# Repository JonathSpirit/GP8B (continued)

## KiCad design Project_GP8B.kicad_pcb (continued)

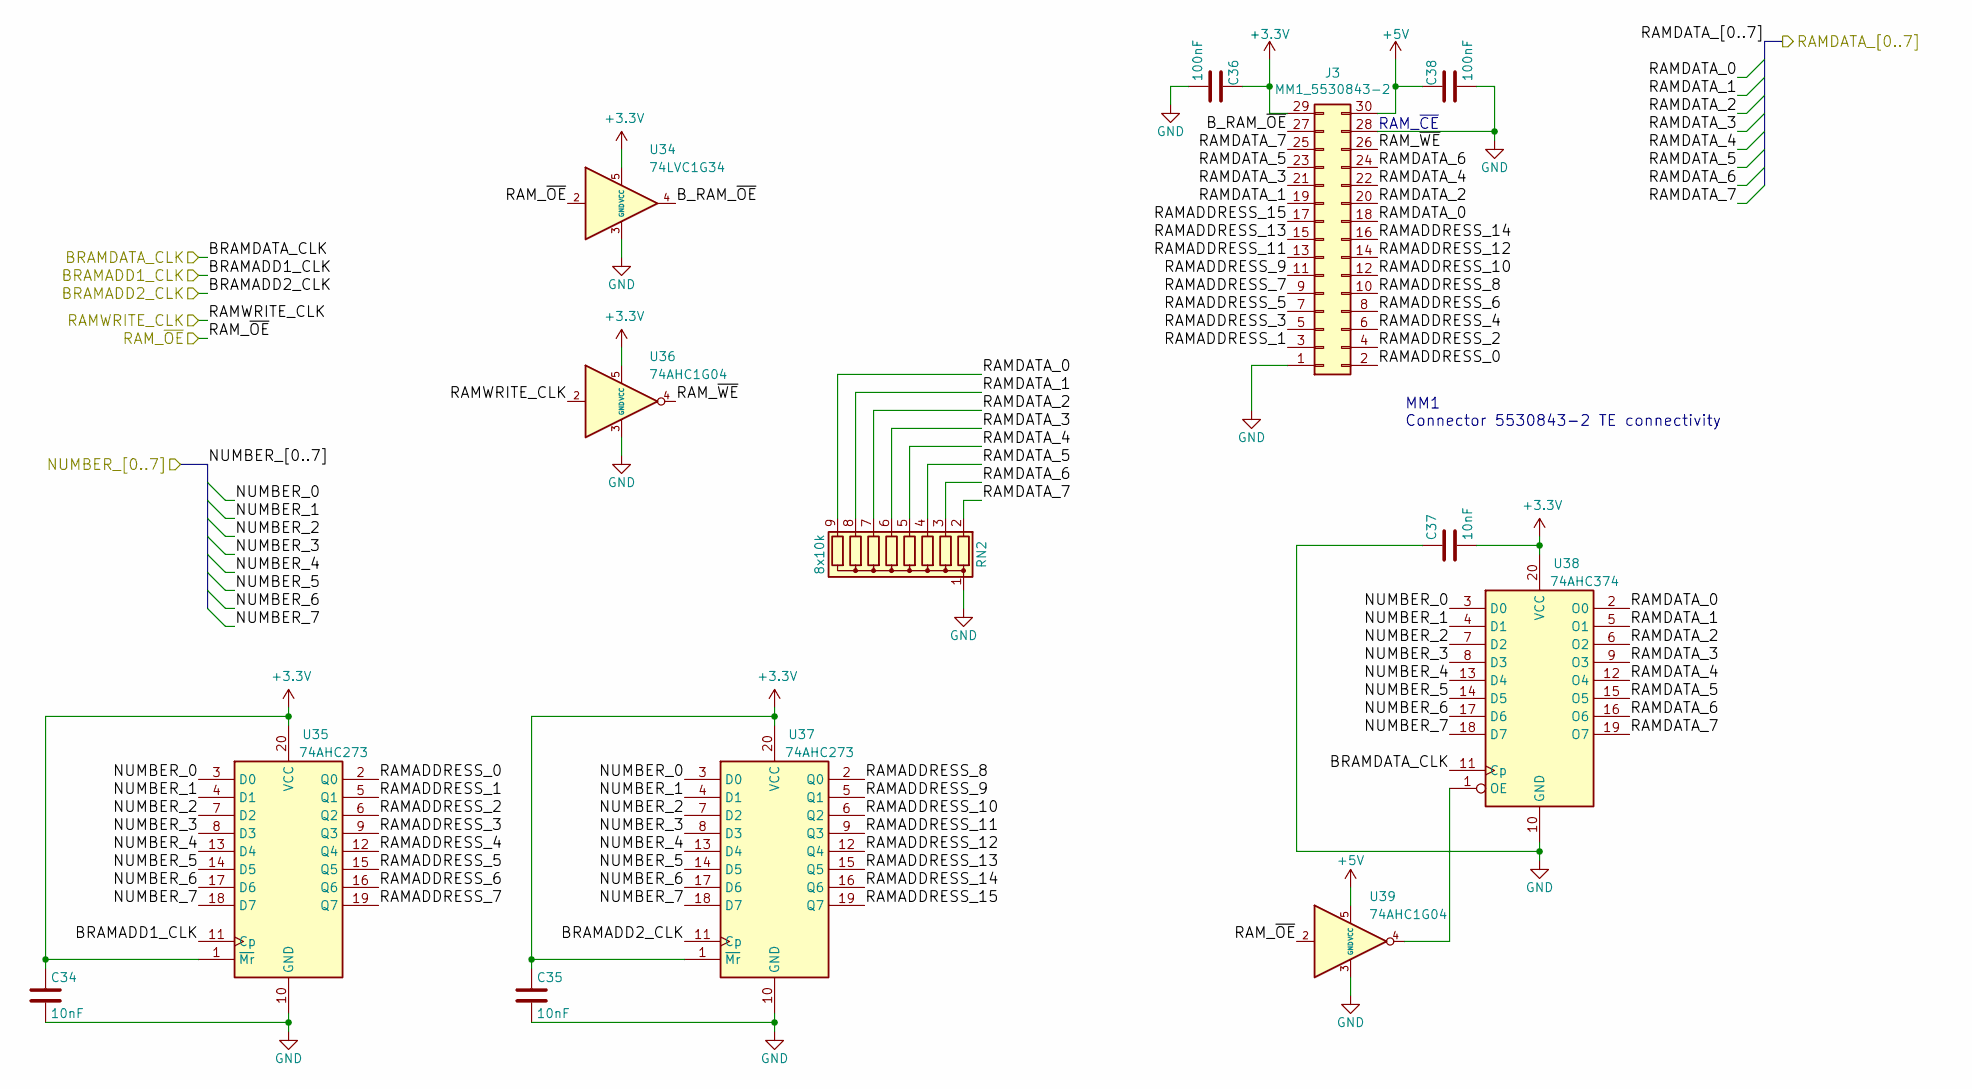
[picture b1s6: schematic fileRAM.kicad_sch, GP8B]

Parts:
C34, C35, C37: 10nF; C_0805_2012Metric
C36, C38: 100nF; C_0805_2012Metric
J3: MM1_5530843-2; TE_5530843-2
RN2: 8x10k; R_Array_SIP9
U34: 74LVC1G34; SOT-23-5
U35, U37: 74AHC273; SOIC-20W_7.5x12.8mm_P1.27mm
U36, U39: 74AHC1G04; SOT-23-5
U38: 74AHC374; SOIC-20W_7.5x12.8mm_P1.27mm

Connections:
+3V3: C34.1, C35.1, C36.1, C37.2, J3.29, U34.5 (VCC), U35.1 (~Mr), U35.20 (VCC), U36.5 (VCC), U37.1 (~Mr), U37.20 (VCC), U38.20 (VCC); also elsewhere on the board
+5V: C38.1, J3.30, U39.5 (VCC); also elsewhere on the board
/BRAMADD1_CLK: U35.11 (Cp); also elsewhere on the board
/BRAMADD2_CLK: U37.11 (Cp); also elsewhere on the board
/BRAMDATA_CLK: U38.11 (Cp); also elsewhere on the board
/NUMBER_0: U35.3 (D0), U37.3 (D0), U38.3 (D0); also elsewhere on the board
/NUMBER_1: U35.4 (D1), U37.4 (D1), U38.4 (D1); also elsewhere on the board
/NUMBER_2: U35.7 (D2), U37.7 (D2), U38.7 (D2); also elsewhere on the board
/NUMBER_3: U35.8 (D3), U37.8 (D3), U38.8 (D3); also elsewhere on the board
/NUMBER_4: U35.13 (D4), U37.13 (D4), U38.13 (D4); also elsewhere on the board
/NUMBER_5: U35.14 (D5), U37.14 (D5), U38.14 (D5); also elsewhere on the board
/NUMBER_6: U35.17 (D6), U37.17 (D6), U38.17 (D6); also elsewhere on the board
/NUMBER_7: U35.18 (D7), U37.18 (D7), U38.18 (D7); also elsewhere on the board
/NumberSelect/RAMDATA_0: J3.18, RN2.9 (R8), U38.2 (O0); also elsewhere on the board
/NumberSelect/RAMDATA_1: J3.19, RN2.8 (R7), U38.5 (O1); also elsewhere on the board
/NumberSelect/RAMDATA_2: J3.20, RN2.7 (R6), U38.6 (O2); also elsewhere on the board
/NumberSelect/RAMDATA_3: J3.21, RN2.6 (R5), U38.9 (O3); also elsewhere on the board
/NumberSelect/RAMDATA_4: J3.22, RN2.5 (R4), U38.12 (O4); also elsewhere on the board
/NumberSelect/RAMDATA_5: J3.23, RN2.4 (R3), U38.15 (O5); also elsewhere on the board
/NumberSelect/RAMDATA_6: J3.24, RN2.3 (R2), U38.16 (O6); also elsewhere on the board
/NumberSelect/RAMDATA_7: J3.25, RN2.2 (R1), U38.19 (O7); also elsewhere on the board
/RAM/B_RAM_~OE: J3.27, U34.4
/RAM/RAMADDRESS_0: J3.2, U35.2 (Q0)
/RAM/RAMADDRESS_1: J3.3, U35.5 (Q1)
/RAM/RAMADDRESS_2: J3.4, U35.6 (Q2)
/RAM/RAMADDRESS_3: J3.5, U35.9 (Q3)
/RAM/RAMADDRESS_4: J3.6, U35.12 (Q4)
/RAM/RAMADDRESS_5: J3.7, U35.15 (Q5)
/RAM/RAMADDRESS_6: J3.8, U35.16 (Q6)
/RAM/RAMADDRESS_7: J3.9, U35.19 (Q7)
/RAM/RAMADDRESS_8: J3.10, U37.2 (Q0)
/RAM/RAMADDRESS_9: J3.11, U37.5 (Q1)
/RAM/RAMADDRESS_10: J3.12, U37.6 (Q2)
/RAM/RAMADDRESS_11: J3.13, U37.9 (Q3)
/RAM/RAMADDRESS_12: J3.14, U37.12 (Q4)
/RAM/RAMADDRESS_13: J3.15, U37.15 (Q5)
/RAM/RAMADDRESS_14: J3.16, U37.16 (Q6)
/RAM/RAMADDRESS_15: J3.17, U37.19 (Q7)
/RAM/RAM_~WE: J3.26, U36.4
/RAMWRITE_CLK: U36.2; also elsewhere on the board
/RAM_OE_CONTROL: U34.2, U39.2; also elsewhere on the board
unnamed: U38.1 (OE), U39.4

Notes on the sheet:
MM1 Connector 5530843-2 TE connectivity
RAM_~{CE}

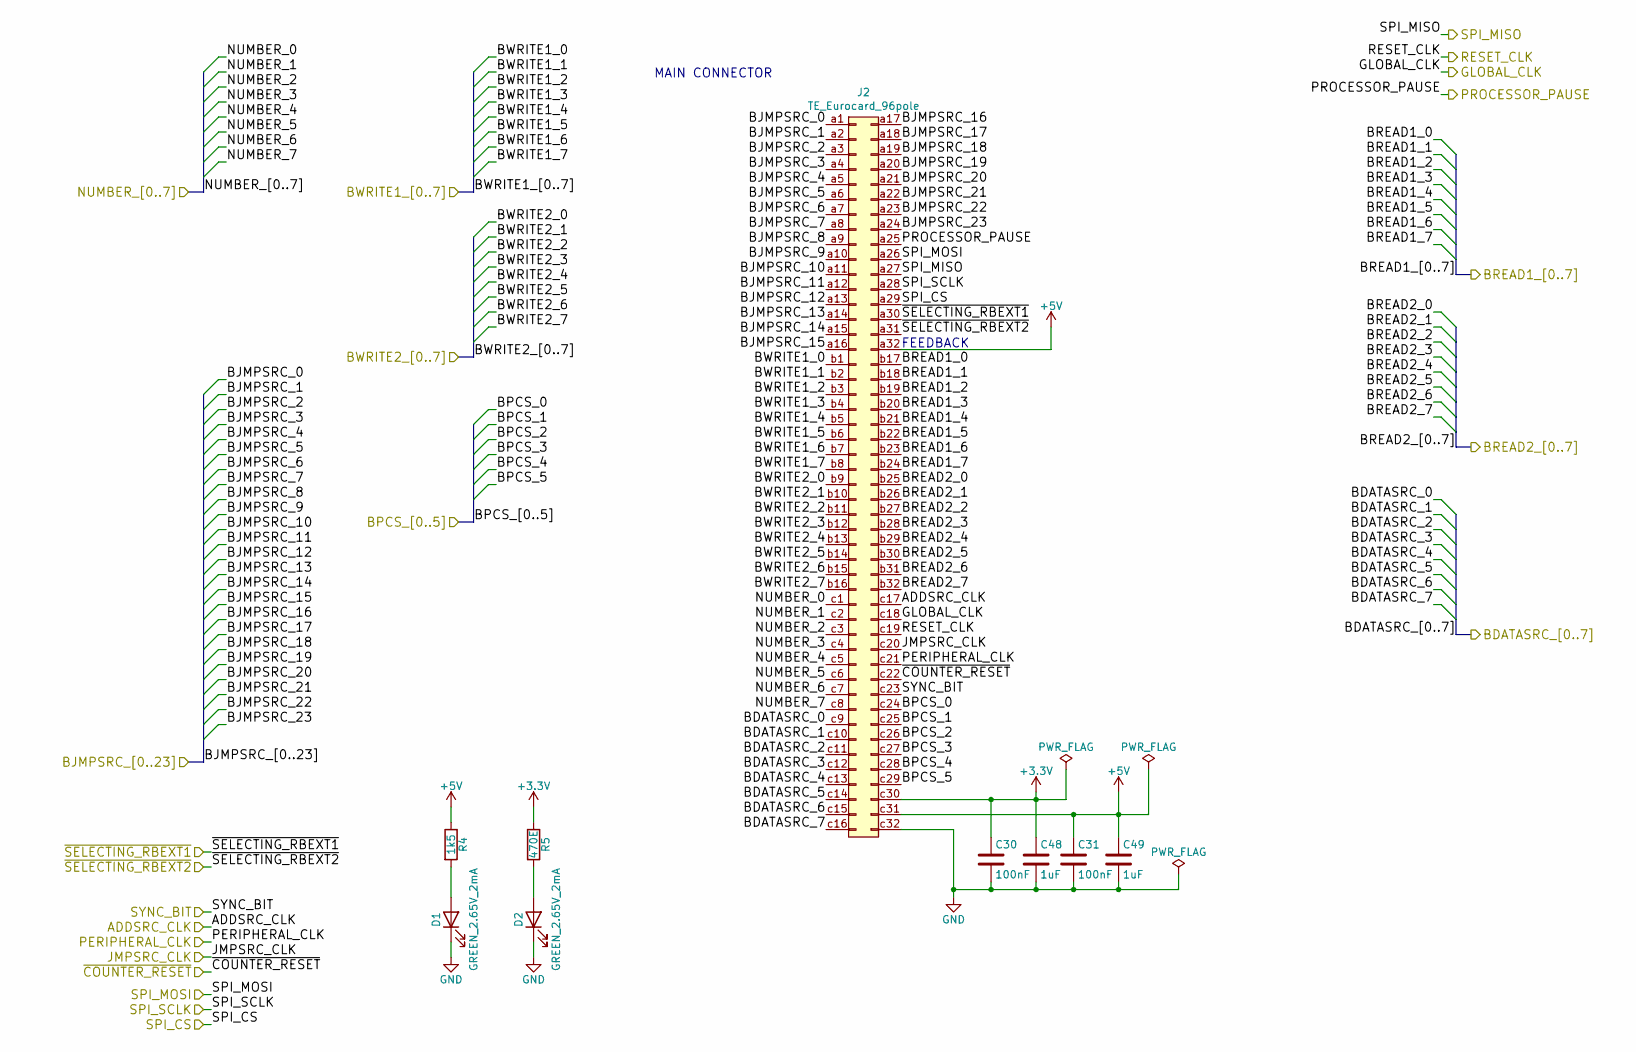
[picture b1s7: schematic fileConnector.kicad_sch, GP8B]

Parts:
C30, C31: 100nF; C_0805_2012Metric
C48, C49: 1uF; C_0805_2012Metric
D1, D2: GREEN_2.65V_2mA; LED_1206_3216Metric
J2: TE_Eurocard_96pole; Eurocard_5536475-1
R4: 1k5; R_0805_2012Metric
R5: 470E; R_0805_2012Metric

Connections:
+3V3: C30.1, C48.1, J2.c30, R5.1; also elsewhere on the board
+5V: C31.1, C49.1, J2.a32, J2.c31, R4.1; also elsewhere on the board
/ADDSRC_CLK: J2.c17; also elsewhere on the board
/Connector/BDATASRC_0: J2.c9; also elsewhere on the board
/Connector/BDATASRC_1: J2.c10; also elsewhere on the board
/Connector/BDATASRC_2: J2.c11; also elsewhere on the board
/Connector/BDATASRC_3: J2.c12; also elsewhere on the board
/Connector/BDATASRC_4: J2.c13; also elsewhere on the board
/Connector/BDATASRC_5: J2.c14; also elsewhere on the board
/Connector/BDATASRC_6: J2.c15; also elsewhere on the board
/Connector/BDATASRC_7: J2.c16; also elsewhere on the board
/Connector/BJMPSRC_0: J2.a1; also elsewhere on the board
/Connector/BJMPSRC_1: J2.a2; also elsewhere on the board
/Connector/BJMPSRC_2: J2.a3; also elsewhere on the board
/Connector/BJMPSRC_3: J2.a4; also elsewhere on the board
/Connector/BJMPSRC_4: J2.a5; also elsewhere on the board
/Connector/BJMPSRC_5: J2.a6; also elsewhere on the board
/Connector/BJMPSRC_6: J2.a7; also elsewhere on the board
/Connector/BJMPSRC_7: J2.a8; also elsewhere on the board
/Connector/BJMPSRC_8: J2.a9; also elsewhere on the board
/Connector/BJMPSRC_9: J2.a10; also elsewhere on the board
/Connector/BJMPSRC_10: J2.a11; also elsewhere on the board
/Connector/BJMPSRC_11: J2.a12; also elsewhere on the board
/Connector/BJMPSRC_12: J2.a13; also elsewhere on the board
/Connector/BJMPSRC_13: J2.a14; also elsewhere on the board
/Connector/BJMPSRC_14: J2.a15; also elsewhere on the board
/Connector/BJMPSRC_15: J2.a16; also elsewhere on the board
/Connector/BJMPSRC_16: J2.a17; also elsewhere on the board
/Connector/BJMPSRC_17: J2.a18; also elsewhere on the board
/Connector/BJMPSRC_18: J2.a19; also elsewhere on the board
/Connector/BJMPSRC_19: J2.a20; also elsewhere on the board
/Connector/BJMPSRC_20: J2.a21; also elsewhere on the board
/Connector/BJMPSRC_21: J2.a22; also elsewhere on the board
/Connector/BJMPSRC_22: J2.a23; also elsewhere on the board
/Connector/BJMPSRC_23: J2.a24; also elsewhere on the board
/Connector/BPCS_0: J2.c24; also elsewhere on the board
/Connector/BPCS_1: J2.c25; also elsewhere on the board
/Connector/BPCS_2: J2.c26; also elsewhere on the board
/Connector/BPCS_3: J2.c27; also elsewhere on the board
/Connector/BPCS_4: J2.c28; also elsewhere on the board
/Connector/BPCS_5: J2.c29; also elsewhere on the board
/Connector/BREAD1_0: J2.b17; also elsewhere on the board
/Connector/BREAD1_1: J2.b18; also elsewhere on the board
/Connector/BREAD1_2: J2.b19; also elsewhere on the board
/Connector/BREAD1_3: J2.b20; also elsewhere on the board
/Connector/BREAD1_4: J2.b21; also elsewhere on the board
/Connector/BREAD1_5: J2.b22; also elsewhere on the board
/Connector/BREAD1_6: J2.b23; also elsewhere on the board
/Connector/BREAD1_7: J2.b24; also elsewhere on the board
/Connector/BREAD2_0: J2.b25; also elsewhere on the board
/Connector/BREAD2_1: J2.b26; also elsewhere on the board
/Connector/BREAD2_2: J2.b27; also elsewhere on the board
/Connector/BREAD2_3: J2.b28; also elsewhere on the board
/Connector/BREAD2_4: J2.b29; also elsewhere on the board
/Connector/BREAD2_5: J2.b30; also elsewhere on the board
/Connector/BREAD2_6: J2.b31; also elsewhere on the board
/Connector/BREAD2_7: J2.b32; also elsewhere on the board
/Connector/BWRITE1_0: J2.b1; also elsewhere on the board
/Connector/BWRITE1_1: J2.b2; also elsewhere on the board
/Connector/BWRITE1_2: J2.b3; also elsewhere on the board
/Connector/BWRITE1_3: J2.b4; also elsewhere on the board
/Connector/BWRITE1_4: J2.b5; also elsewhere on the board
/Connector/BWRITE1_5: J2.b6; also elsewhere on the board
/Connector/BWRITE1_6: J2.b7; also elsewhere on the board
/Connector/BWRITE1_7: J2.b8; also elsewhere on the board
/Connector/BWRITE2_0: J2.b9; also elsewhere on the board
/Connector/BWRITE2_1: J2.b10; also elsewhere on the board
/Connector/BWRITE2_2: J2.b11; also elsewhere on the board
/Connector/BWRITE2_3: J2.b12; also elsewhere on the board
/Connector/BWRITE2_4: J2.b13; also elsewhere on the board
/Connector/BWRITE2_5: J2.b14; also elsewhere on the board
/Connector/BWRITE2_6: J2.b15; also elsewhere on the board
/Connector/BWRITE2_7: J2.b16; also elsewhere on the board
/GLOBAL_CLK: J2.c18; also elsewhere on the board
/JMPSRC_CLK: J2.c20; also elsewhere on the board
/NUMBER_0: J2.c1; also elsewhere on the board
/NUMBER_1: J2.c2; also elsewhere on the board
/NUMBER_2: J2.c3; also elsewhere on the board
/NUMBER_3: J2.c4; also elsewhere on the board
/NUMBER_4: J2.c5; also elsewhere on the board
/NUMBER_5: J2.c6; also elsewhere on the board
/NUMBER_6: J2.c7; also elsewhere on the board
/NUMBER_7: J2.c8; also elsewhere on the board
/PERIPHERAL_CLK: J2.c21; also elsewhere on the board
/PROCESSOR_PAUSE: J2.a25; also elsewhere on the board
/RESET_CLK: J2.c19; also elsewhere on the board
/SPI_CS: J2.a29; also elsewhere on the board
/SPI_MISO: J2.a27; also elsewhere on the board
/SPI_MOSI: J2.a26; also elsewhere on the board
/SPI_SCLK: J2.a28; also elsewhere on the board
/SYNC_BIT: J2.c23; also elsewhere on the board
/~COUNTER_RESET: J2.c22; also elsewhere on the board
/~SELECTING_RBEXT1: J2.a30; also elsewhere on the board
/~SELECTING_RBEXT2: J2.a31; also elsewhere on the board
unnamed: D1.2 (A), R4.2
unnamed: D2.2 (A), R5.2

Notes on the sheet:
MAIN CONNECTOR
FEEDBACK

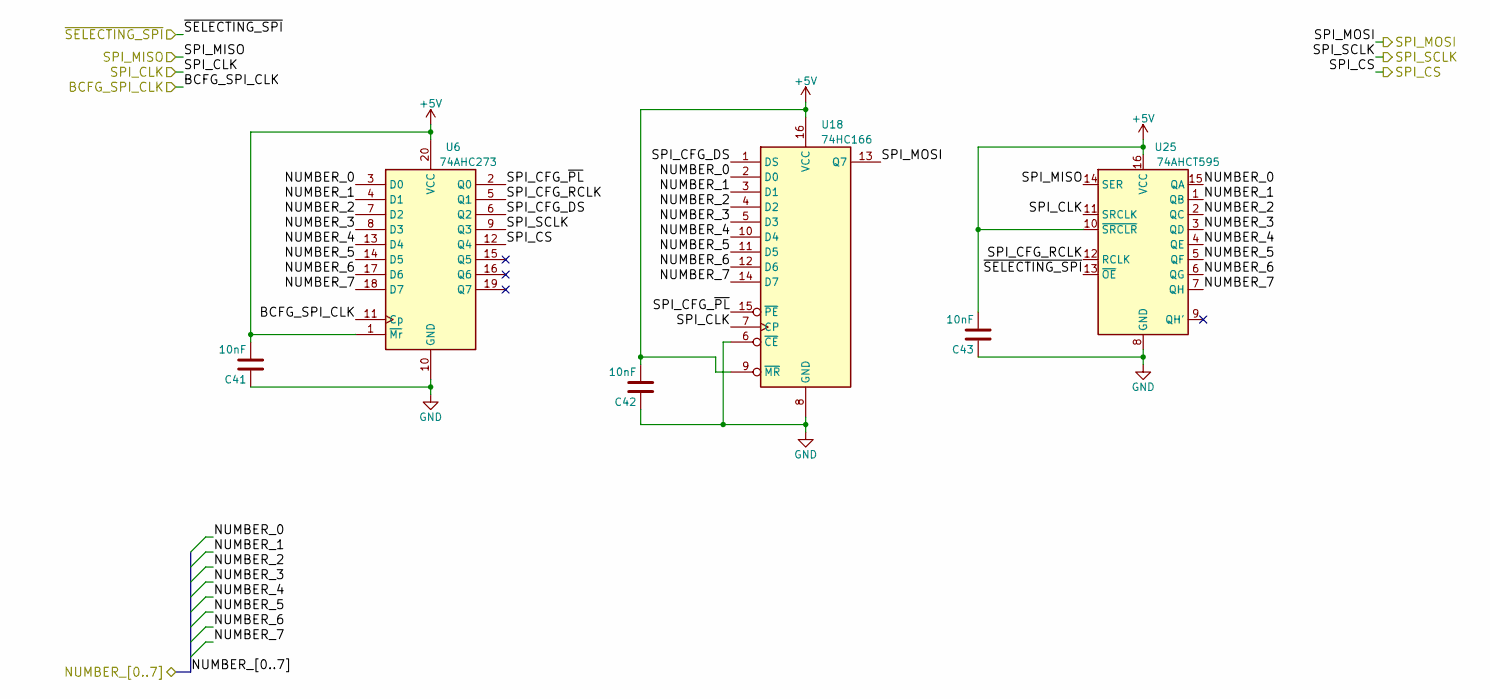
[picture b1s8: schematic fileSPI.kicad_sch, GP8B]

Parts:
C41, C42, C43: 10nF; C_0805_2012Metric
U6: 74AHC273; SOIC-20W_7.5x12.8mm_P1.27mm
U18: 74HC166; SOIC-16_3.9x9.9mm_P1.27mm
U25: 74AHCT595; SOIC-16_3.9x9.9mm_P1.27mm

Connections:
+5V: C41.2, C42.2, C43.2, U6.1 (~Mr), U6.20 (VCC), U18.9 (~MR), U18.16 (VCC), U25.10 (~SRCLR), U25.16 (VCC); also elsewhere on the board
/BCFG_SPI_CLK: U6.11 (Cp); also elsewhere on the board
/NUMBER_0: U6.3 (D0), U18.2 (D0), U25.15 (QA); also elsewhere on the board
/NUMBER_1: U6.4 (D1), U18.3 (D1), U25.1 (QB); also elsewhere on the board
/NUMBER_2: U6.7 (D2), U18.4 (D2), U25.2 (QC); also elsewhere on the board
/NUMBER_3: U6.8 (D3), U18.5 (D3), U25.3 (QD); also elsewhere on the board
/NUMBER_4: U6.13 (D4), U18.10 (D4), U25.4 (QE); also elsewhere on the board
/NUMBER_5: U6.14 (D5), U18.11 (D5), U25.5 (QF); also elsewhere on the board
/NUMBER_6: U6.17 (D6), U18.12 (D6), U25.6 (QG); also elsewhere on the board
/NUMBER_7: U6.18 (D7), U18.14 (D7), U25.7 (QH); also elsewhere on the board
/SPI/SPI_CFG_DS: U6.6 (Q2), U18.1 (DS)
/SPI/SPI_CFG_RCLK: U6.5 (Q1), U25.12 (RCLK)
/SPI/SPI_CFG_~PL: U6.2 (Q0), U18.15 (~PE)
/SPI_CLK: U18.7 (CP), U25.11 (SRCLK); also elsewhere on the board
/SPI_CS: U6.12 (Q4); also elsewhere on the board
/SPI_MISO: U25.14 (SER); also elsewhere on the board
/SPI_MOSI: U18.13 (Q7); also elsewhere on the board
/SPI_SCLK: U6.9 (Q3); also elsewhere on the board
/~SELECTING_SPI: U25.13 (~OE); also elsewhere on the board

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
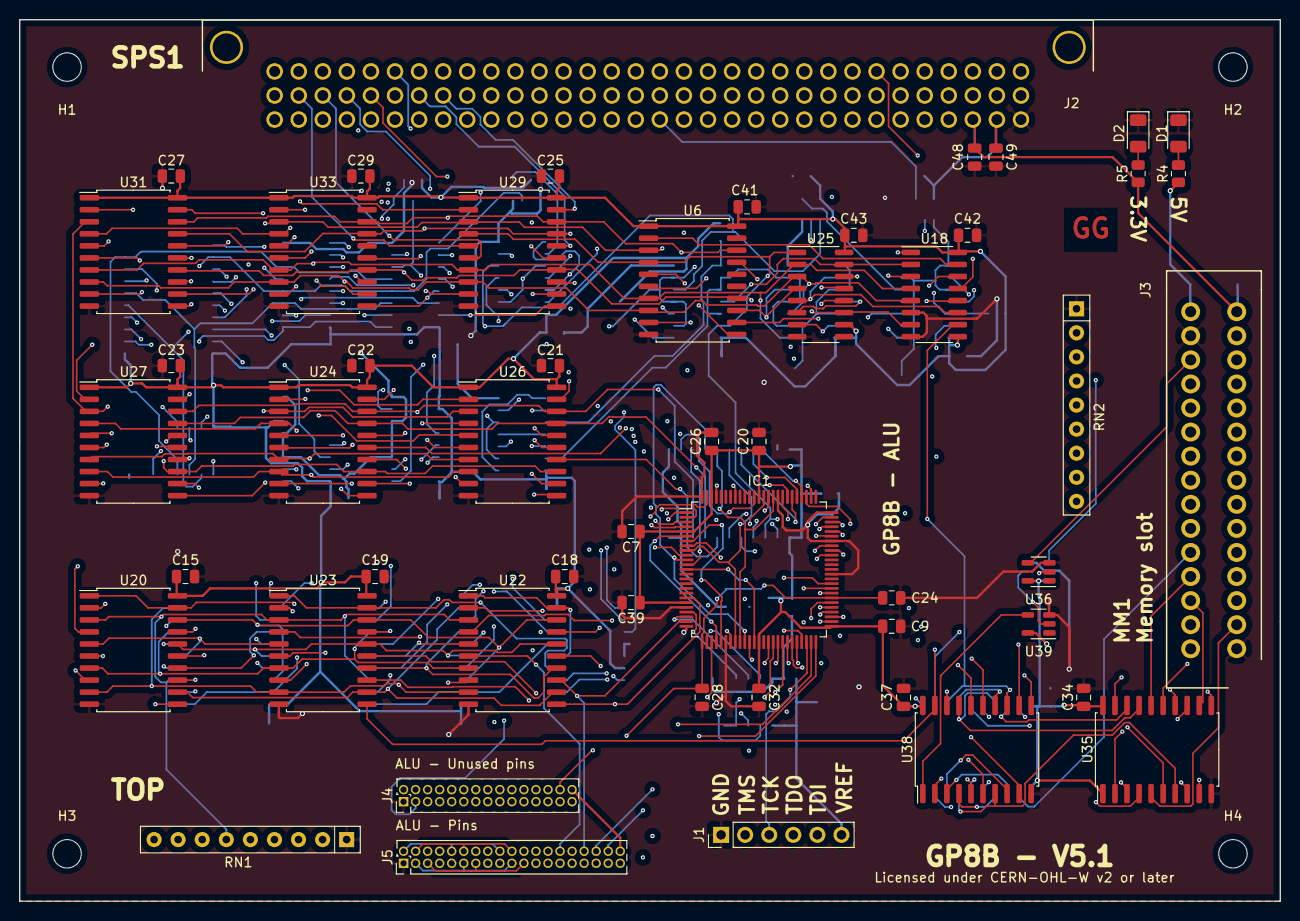
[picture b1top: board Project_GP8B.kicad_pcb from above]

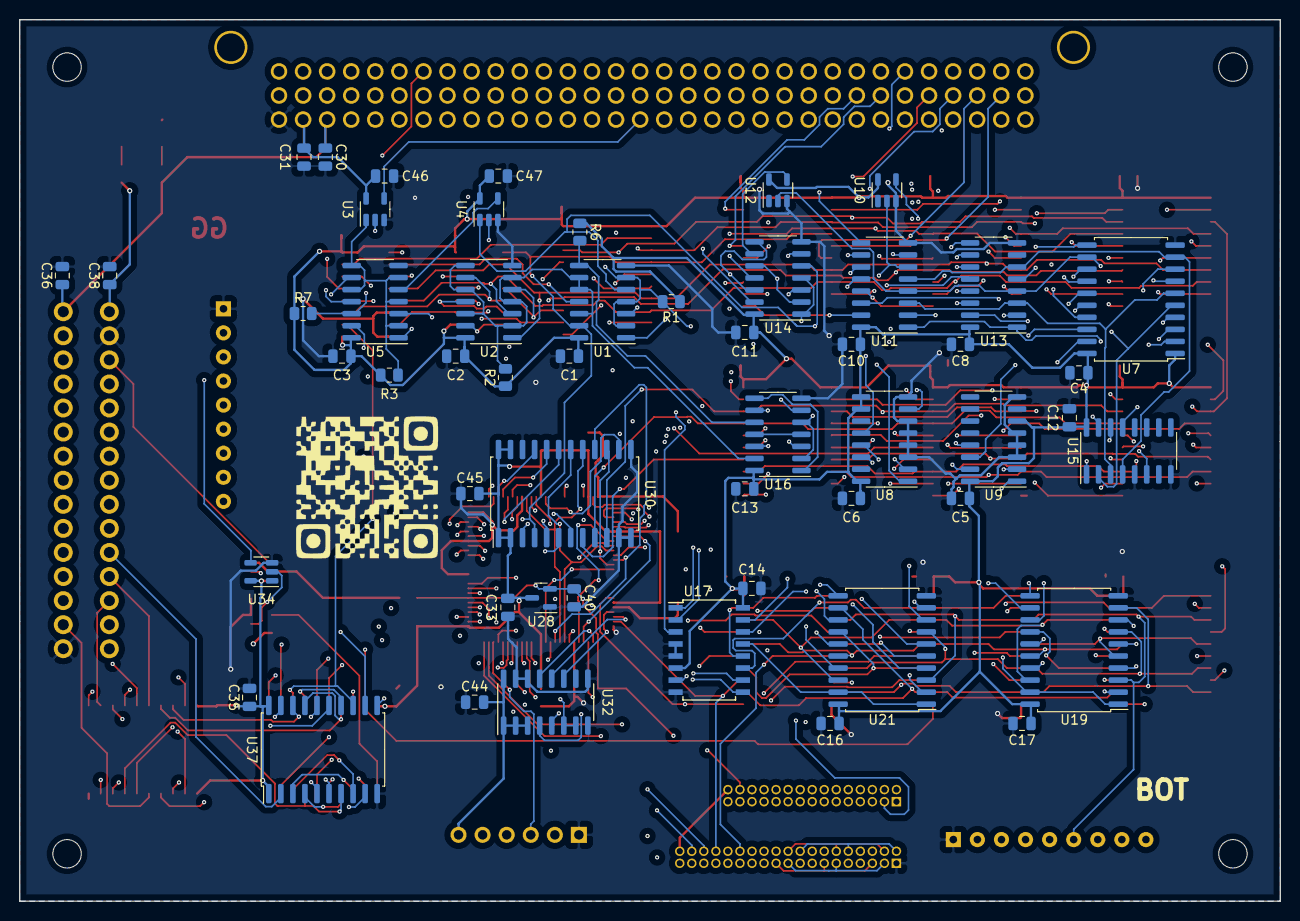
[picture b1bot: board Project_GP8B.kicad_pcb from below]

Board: 4 copper layers, 133.0 x 93.0 mm, 109 parts (53 on the bottom side), 229 nets.

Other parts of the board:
C46: 10nF; C_0805_2012Metric
U3: 74AHC1G02; SOT-23-5

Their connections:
+5V: C46.2, U3.5; also elsewhere on the board
/ADDSRC_CLK: U3.4; also elsewhere on the board
/GLOBAL_CLK: U3.2; also elsewhere on the board

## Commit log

2020-01-09 initial upload
2020-01-30 cleaning
2020-02-21 Create LICENCE
2020-02-21 Rename LICENCE to LICENSE
2020-02-21 Adding license info on silks
2020-03-09 Adding copyright and license notice
2020-04-11 Adding schematics in PDF
2020-04-11 Adding schematics (.pdf)
2020-05-18 Small documents cleaning
2020-05-18 Creation of the datasheet (WIP)
2020-05-20 Adding sequencer waveform, datasheet progress
2020-05-23 Datasheet progress
2020-05-23 Small symbols changes, CHANGELOG, TPS7A0518PDBZR
2020-05-23 Replacing CPLD, add 1.8V regulator, see CHANGELOG
2020-05-23 Adding JTAG change to CHANGELOG
2020-05-26 Switching license to "CERN-OHLw v2 or later"
2020-05-26 Renaming "librairies" to "libraries"
2020-05-26 Adding SN74LVC8T245DW and SN74AVC4T245D
2020-06-02 Small fix/work-around for SPI
2020-06-02 Removing weird/old component file
2020-06-02 Modify CHANGELOG
2020-06-02 Removing old symbols and unused footprints
2020-06-02 Small clean and mounting holes
2020-06-02 Renaming files, cleaning, CHANGELOG
2020-06-02 Removing duplication
2020-06-09 Updating materials list
2020-06-09 Netlist update
2020-06-09 Preparing footprint placement, removing old footprint
2020-06-09 Exporting new schematics in PDF
2020-06-19 Footprints placement
2020-06-30 Renaming blockDiagram and modify it for v5.0
2020-06-30 Finishing material list
2020-07-01 Removing .rpt file
2020-07-01 Adding QRCode
2020-07-01 Fixing 3D for TE_5530843-2
2020-07-01 Finishing the new PCB
2020-07-01 Exporting new pcb to Gerbert,drl files
2020-07-01 Exporting new PCB to pdf for fabrication
2020-07-01 Renaming "Waveforms" to "waveforms"
2020-07-01 Changelog : QRCode, fixing 3D
2020-07-01 Renaming GP8B_Datasheet.odt to GP8B_datasheet.odt and datasheet progress
2020-07-01 Remove duplication
2020-07-01 New images
2020-07-01 Exporting material list to pdf
2020-08-11 Revision 1 of the datasheet, .fodt format
2020-08-11 .fods format for the materials
2020-08-11 Replacing tabs with spaces, cleaning
2020-08-11 datasheet .pdf
2020-08-14 Apply MM1 memory standard, and shared power pin symbol fix
2020-08-14 Regenerate Gerbert files
2020-08-18 Revert SPI 4bits problem work-around (finally this fixed nothing)
2020-08-18 GP8B_blockDiagram.odg is now in .fodg format
2020-08-18 Regenerating gerbert files
2020-08-18 Update materials list
2020-08-18 Apply date (19.08.2020), QRcode fix
2020-08-18 Exporting schematics (.pdf)
2020-08-18 Exporting pcb placement (.pdf)
2020-08-18 Exporting images
2020-09-23 Shifting J4 and J5 they were off the sheet.
2020-09-23 Adding RAM ALU details, and improvement of the datasheet
2021-02-12 wait the 5.1 release
2021-03-04 Apply new symbol for XC2C256-VQ100 #5
2021-03-04 Set new date and 5.1
2021-03-04 Replacing 74HC165 with 74HC166, and add SPI_CFG_DS #4
2021-03-04 Replace some gates with a 74AHC1G02 to fix the pulse problem #3
2021-03-05 Go next only if SRCVALUE, (simple instruction)
2021-03-05 Remove weird ghost bus in register
2021-03-05 Small cleaning in fileRegister
2021-03-05 Go next only if SRCVALUE, (complex instruction) #8 adding 74AHC1G08
2021-03-05 Better decoupling #6
2021-03-05 Component association (#7)
2021-03-05 netlist
2021-05-27 Updated BOM for V5.1
2021-05-31 Routing, cleaning first pass
2021-07-12 bit of pcb cleaning
2021-07-12 SolderMaskClearance to 0
2021-07-12 Schematics to pdf
2021-07-12 PCB files in pdf
2021-07-12 exporting Gerbert files
2021-07-12 new 3d images
2021-10-11 Modifying CHANGELOG file
2021-10-11 V5.1 (#9)
    * Apply new symbol for XC2C256-VQ100 #5
    * Set new date and 5.1
    * Replacing 74HC165 with 74HC166, and add SPI_CFG_DS #4
    * Replace some gates with a 74AHC1G02 to fix the pulse problem #3
    * Go next only if SRCVALUE, (simple instruction)
    * Remove weird ghost bus in register
2021-11-08 Update README.md
    https://forum.kicad.info/t/warning-avoid-all-links-to-kicad-pcb-org-use-kicad-org/31521
2022-07-08 Transition to kicad version 6
2022-07-08 Updating descriptions
2022-09-20 convert custom lib to new kicad format
2022-09-20 Renaming COUNTER to SEQUENCE and others to make it clear
2022-09-21 Add more sequences to prepare 50MHz compatibility (removing clock sync)
2022-09-21 Finally remove clock sync, big improvement for the "if" instruction check (faster tps, less gates)
2022-09-21 bit of cleaning after last commit
2023-03-18 updating to kicad 7, fix 3d model of Eurocard_5536475-1
2023-03-18 updating wavedrom_sequencer
2023-03-18 updating symbols ref, renaming some pins (NEXT_AFTERSET -> REQ_NEXT_AFTERISET)
2023-03-18 replace 74LS163 to 74LVC163 in order to reduce Tpd, with this replacement, CD74AC238 must be change to CD74ACT238
2023-08-10 replacing 10k pull-ups resistors with 1k in order to limit the effect on rise up time
2023-08-10 add a simulation with circuit verse
2023-08-11 update copyright date, replacing LVC163 -> LV163.
2023-08-20 update BOM
2024-07-25 update CD74AC238 ref
